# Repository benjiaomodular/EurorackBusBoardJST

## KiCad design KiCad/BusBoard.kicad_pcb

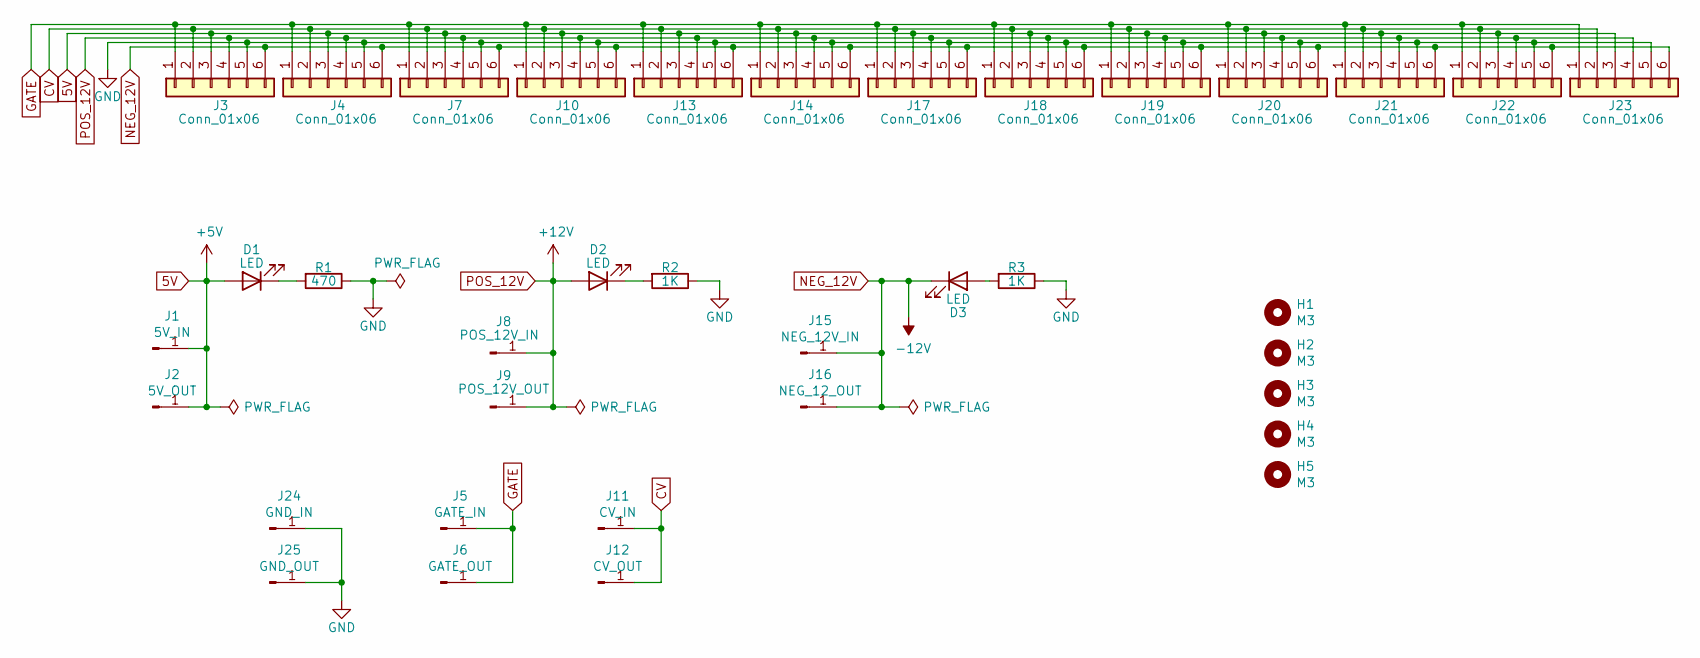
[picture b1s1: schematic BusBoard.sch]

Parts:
D1, D2, D3: LED; LED_D3.0mm
H1, H2, H3, H4, H5: M3; MountingHole_3.2mm_M3
J1: 5V_IN; SolderWire-0.5sqmm_1x01_D0.9mm_OD2.3mm
J2: 5V_OUT; SolderWire-0.5sqmm_1x01_D0.9mm_OD2.3mm
J3, J4, J7, J10, J13, J14, J17, J18, J19, J20, J21, J22, J23: Conn_01x06; JST_XH_B6B-XH-A_1x06_P2.50mm_Vertical
J5: GATE_IN; SolderWire-0.5sqmm_1x01_D0.9mm_OD2.3mm
J6: GATE_OUT; SolderWire-0.5sqmm_1x01_D0.9mm_OD2.3mm
J8: POS_12V_IN; SolderWire-0.5sqmm_1x01_D0.9mm_OD2.3mm
J9: POS_12V_OUT; SolderWire-0.5sqmm_1x01_D0.9mm_OD2.3mm
J11: CV_IN; SolderWire-0.5sqmm_1x01_D0.9mm_OD2.3mm
J12: CV_OUT; SolderWire-0.5sqmm_1x01_D0.9mm_OD2.3mm
J15: NEG_12V_IN; SolderWire-0.5sqmm_1x01_D0.9mm_OD2.3mm
J16: NEG_12_OUT; SolderWire-0.5sqmm_1x01_D0.9mm_OD2.3mm
J24: GND_IN; SolderWire-0.5sqmm_1x01_D0.9mm_OD2.3mm
J25: GND_OUT; SolderWire-0.5sqmm_1x01_D0.9mm_OD2.3mm
R1: 470; Resistor_L6.3mm_D2.5mm_P7.62mm_Horizontal
R2, R3: 1K; Resistor_L6.3mm_D2.5mm_P7.62mm_Horizontal

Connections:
5V: D1.2 (A), J1.1, J2.1, J3.3, J4.3, J7.3, J10.3, J13.3, J14.3, J17.3, J18.3, J19.3, J20.3, J21.3, J22.3, J23.3
CV: J3.2, J4.2, J7.2, J10.2, J11.1, J12.1, J13.2, J14.2, J17.2, J18.2, J19.2, J20.2, J21.2, J22.2, J23.2
GATE: J3.1, J4.1, J5.1, J6.1, J7.1, J10.1, J13.1, J14.1, J17.1, J18.1, J19.1, J20.1, J21.1, J22.1, J23.1
GND: J3.5, J4.5, J7.5, J10.5, J13.5, J14.5, J17.5, J18.5, J19.5, J20.5, J21.5, J22.5, J23.5, J24.1, J25.1, R1.1, R2.1, R3.1
NEG_12V: D3.1 (K), J3.6, J4.6, J7.6, J10.6, J13.6, J14.6, J15.1, J16.1, J17.6, J18.6, J19.6, J20.6, J21.6, J22.6, J23.6
unnamed: D1.1 (K), R1.2
unnamed: D2.1 (K), R2.2
unnamed: D3.2 (A), R3.2
POS_12V: D2.2 (A), J3.4, J4.4, J7.4, J8.1, J9.1, J10.4, J13.4, J14.4, J17.4, J18.4, J19.4, J20.4, J21.4, J22.4, J23.4

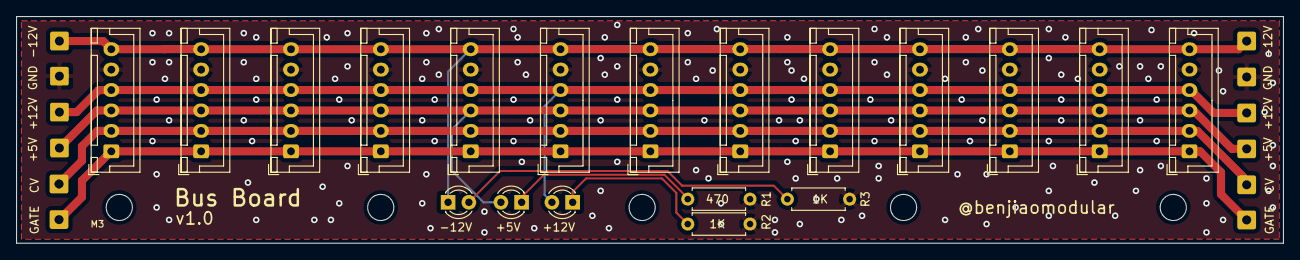
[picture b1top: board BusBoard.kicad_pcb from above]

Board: 2 copper layers, 155.1 x 27.8 mm, 36 parts (0 on the bottom side), 9 nets.

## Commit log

2022-05-16 Added gitignore
2022-05-16 Removed bak files
